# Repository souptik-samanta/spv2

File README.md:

# SoupPad (SPV2)

> A custom mechanical macropad by Souptik — featuring 6 switches, a rotary encoder, an OLED display, and a Seeed Studio XIAO microcontroller.

---

## preview 

---

## Features

- 6 keys 
- 1 encoder 
- 1 oled 
- works on a xiao

---

### What You'll Need

- Custom PCB (order from JLCPCB, PCBWay, etc. using the gerbers)
- Seeed Studio XIAO (any variant)
- 6x MX-compatible switches
- 6x keycaps
- 1x rotary encoder + knob
- 1x small OLED screen
- 3D printed case (print the STL files)
- M3 screws and nuts
- USB-C cable

### Assembly Steps

1. Print the case using PLA 
2. solder the PCB — place switches, encoder, display, and XIAO
3. Flash the firmware onto the XIAO
4. Assemble — screw the PCB into the case
5. Plug in and configure your macros!

---
Name | link | quantity | price | price quantity | vendor | status
-- | -- | -- | -- | -- | -- | --
keycaps | N/a | 6 | N/a | N/a | self | aquired
cherry mx | N/a | 6 | N/a | N/a | self | aquired
pcb | jlcpcb.com | 1 | 11 | 11 | jlcpcb | planing
case | N/a | 1x | 50cent | 50 | self | made
SSD1306 oled | https://quartzcomponents.com/products/oled-display-0-96-inch-i2c-interface-4-pin-blue-ssd1306?variant=33049183060103&country=IN&currency=INR&utm_medium=product_sync&utm_source=google&utm_content=sag_organic&utm_campaign=sag_organic?utm_source=google&utm_medium=FreeListings&srsltid=AfmBOorsbj_mcdhpm64q1XpYrVHl3aL0RwTseDNoNrqtfPXqM2rrpq4e13g | 1 | 150Rs | 150 | quartz | planing
EC11 encoder | https://probots.co.in/20-position-360-degree-rotary-encoder-ec11-w-push-button.html | 1 | 100 | 100 | probots | planing
Xiao seeed | https://robocraze.com/products/seeed-studio-xiao-esp32c3 | 1 | 600 | 600 | robocrze | planing
4148 diode | https://www.electricallearner.in/product/1n4148-diode-500mw-100v-glass-diode/?srsltid=AfmBOoqRdRb2OJyy0Yj-ITs9MlDKtWR0Jx_fuFhAGuW4U9hnSnFMeYqCdQs | 1 | 100 | 100 | electriclearner | planing
m3 nuts botls screws | 3d print | idk | 0 | 0 | 3dp | done

# Working video
[YT](https://youtu.be/pELqTFTqWHc)
> *SoupPad V2 — because i need a cool thing on my desk.*

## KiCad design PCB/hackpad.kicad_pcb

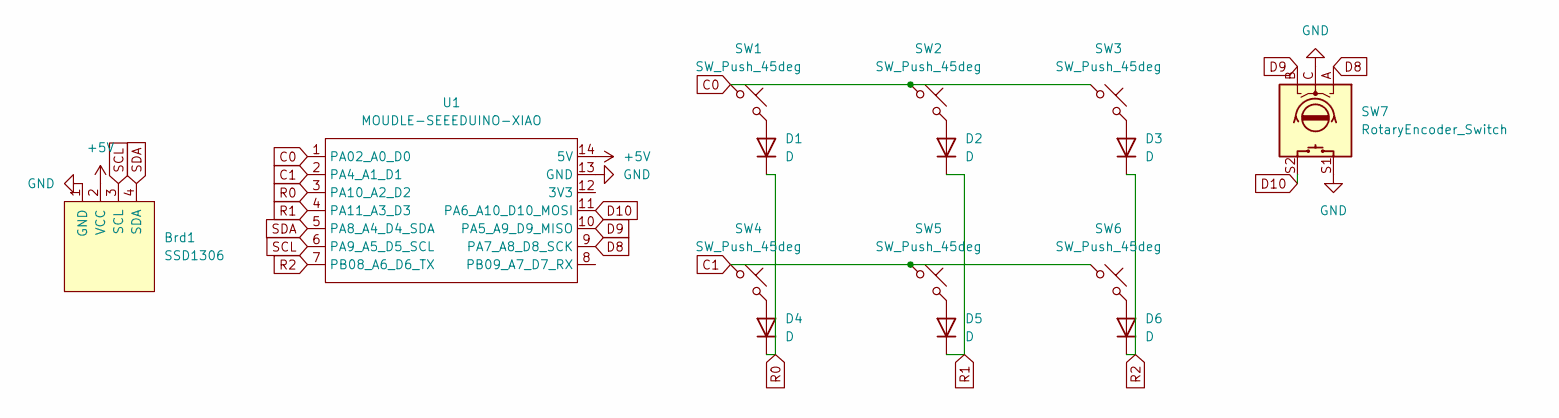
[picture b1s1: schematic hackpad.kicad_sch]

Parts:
Brd1: SSD1306; 128x64OLED
D1, D2, D3, D4, D5, D6: D; D_DO-35_SOD27_P7.62mm_Horizontal
SW1, SW2, SW3, SW4, SW5, SW6: SW_Push_45deg; SW_Cherry_MX_1.00u_PCB
SW7: RotaryEncoder_Switch; RotaryEncoder_Alps_EC12E-Switch_Vertical_H20mm
U1: MOUDLE-SEEEDUINO-XIAO; XIAO-Generic-Hybrid-14P-2.54-21X17.8MM

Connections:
+5V: Brd1.2 (VCC), U1.14 (5V)
C0: SW1.1, SW2.1, SW3.1, U1.1 (PA02_A0_D0)
C1: SW4.1, SW5.1, SW6.1, U1.2 (PA4_A1_D1)
D8: SW7.A, U1.9 (PA7_A8_D8_SCK)
D9: SW7.B, U1.10 (PA5_A9_D9_MISO)
D10: SW7.S2, U1.11 (PA6_A10_D10_MOSI)
GND: Brd1.1 (GND), SW7.C, SW7.S1, U1.13 (GND)
unnamed: D1.2 (A), SW1.2
unnamed: D2.2 (A), SW2.2
unnamed: D3.2 (A), SW3.2
unnamed: D4.2 (A), SW4.2
unnamed: D5.2 (A), SW5.2
unnamed: D6.2 (A), SW6.2
R0: D1.1 (K), D4.1 (K), U1.3 (PA10_A2_D2)
R1: D2.1 (K), D5.1 (K), U1.4 (PA11_A3_D3)
R2: D3.1 (K), D6.1 (K), U1.7 (PB08_A6_D6_TX)
SCL: Brd1.3 (SCL), U1.6 (PA9_A5_D5_SCL)
SDA: Brd1.4 (SDA), U1.5 (PA8_A4_D4_SDA)

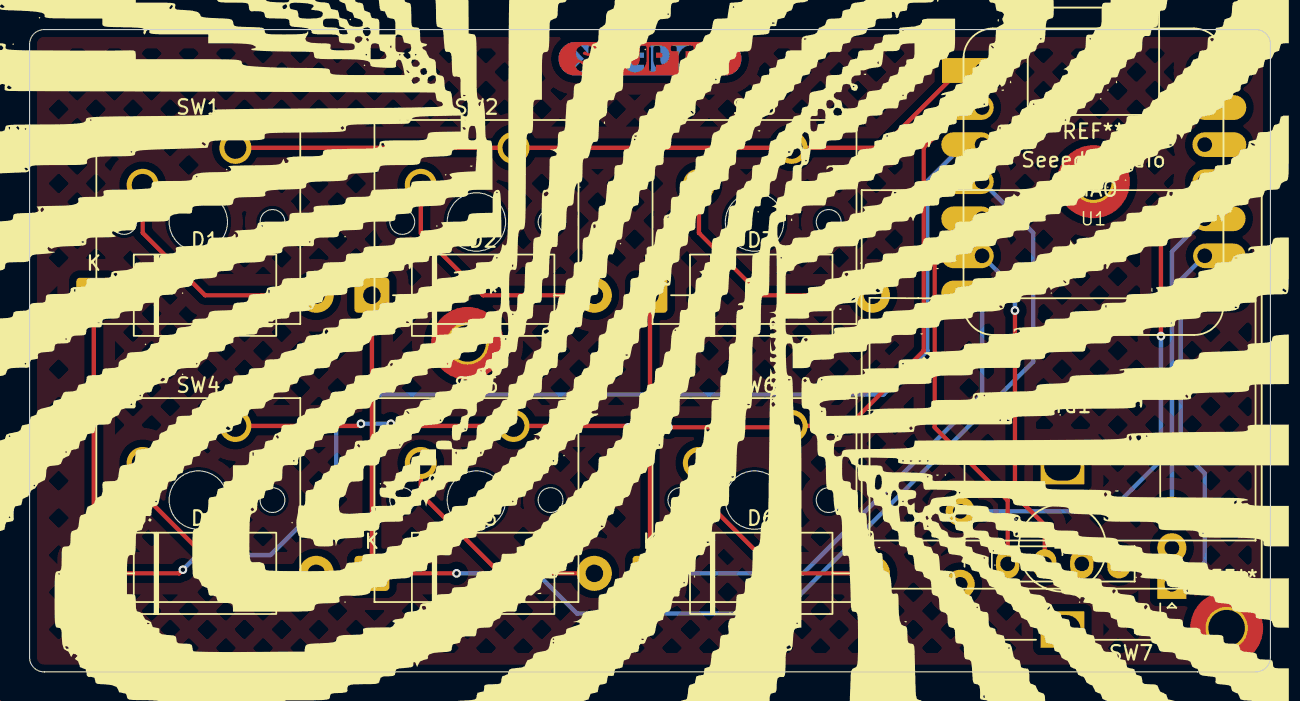
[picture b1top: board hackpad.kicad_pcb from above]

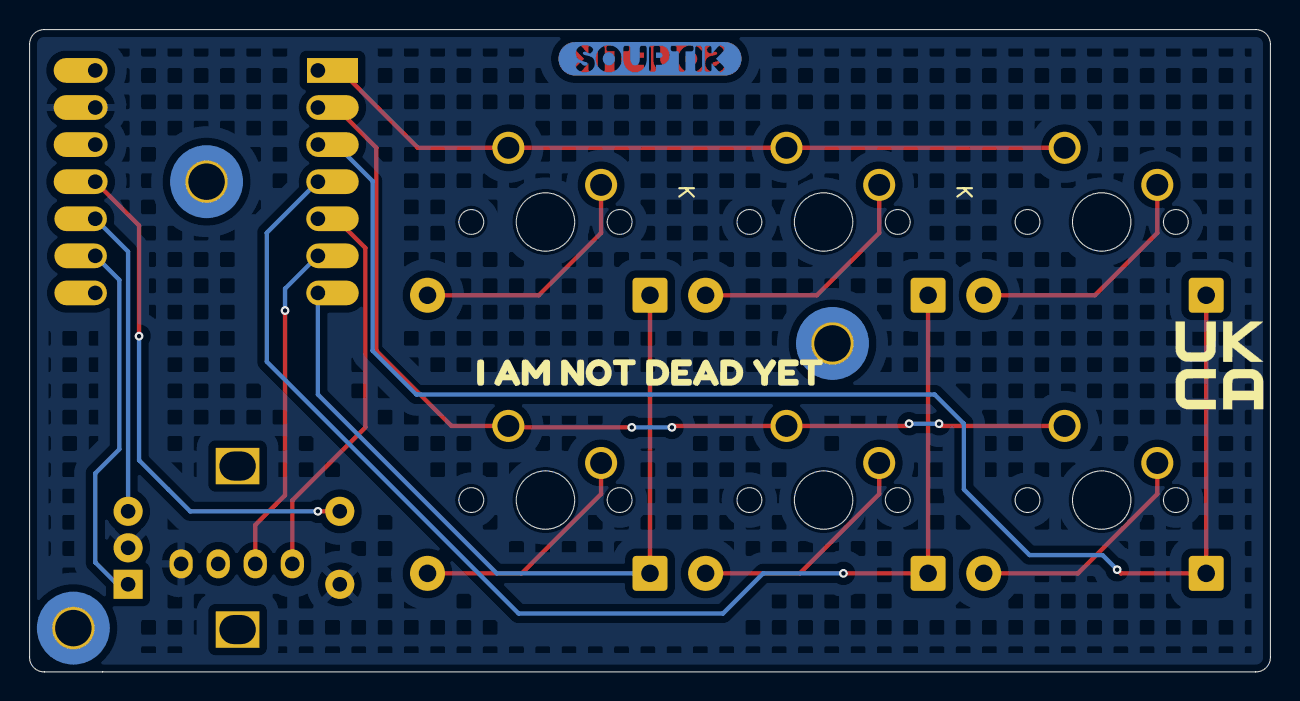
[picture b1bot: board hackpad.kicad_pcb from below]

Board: 2 copper layers, 85.0 x 44.0 mm, 20 parts (3 on the bottom side), 18 nets.

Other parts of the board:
kibuzzard-69AC02E9, kibuzzard-69AC02E9#2: G***; kibuzzard-69AC02E9
kibuzzard-69AC06C1: G***; kibuzzard-69AC06C1
kibuzzard-69AC031A, kibuzzard-69AC031A#2: G***; kibuzzard-69AC031A

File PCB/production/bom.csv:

Designator,Footprint,Quantity,Value,LCSC Part #
BRD1,128x64OLED,1,SSD1306,
"D1, D2, D3, D4, D5, D6",D_DO-27_P15.24mm_Horizontal,6,D,
"SW1, SW2, SW3, SW4, SW5, SW6",SW_Cherry_MX_1.00u_PCB_model,6,SW_Push_45deg,
SW7,RotaryEncoder_Alps_EC12E-Switch_Vertical_H20mm,1,RotaryEncoder_Switch,
U1,XIAO-Generic-Hybrid-14P-2.54-21X17.8MM,1,MOUDLE-SEEEDUINO-XIAO,

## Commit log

2026-02-19 pcb done
2026-02-22 code
2026-02-27 eyeyey
2026-03-18 WORKING PIC
2026-03-18 RADME
2026-04-20 Done
